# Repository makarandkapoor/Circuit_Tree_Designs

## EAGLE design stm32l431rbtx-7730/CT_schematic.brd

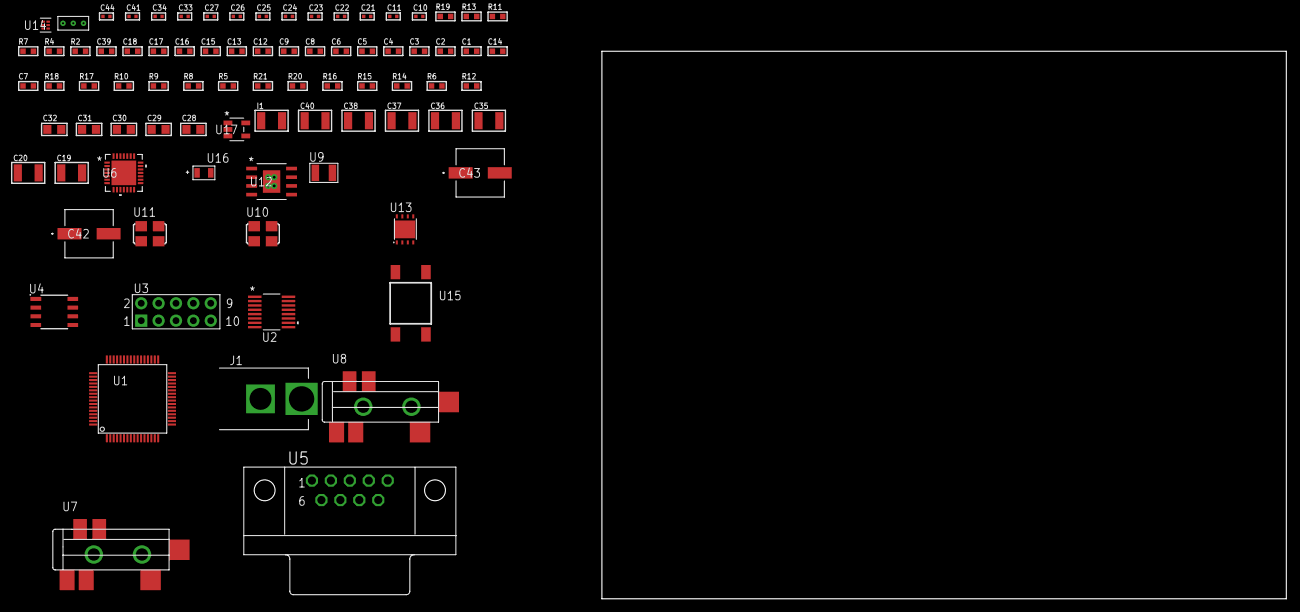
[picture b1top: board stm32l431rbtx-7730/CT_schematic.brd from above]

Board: 2 copper layers, 100.0 x 80.0 mm, 83 parts (0 on the bottom side), 45 nets, no tracks yet.

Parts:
C1, C9, C12, C13, C15, C16, C17, C18, C39: 1e-06; C0603
C2, C3, C4, C5, C6: 1e-07; C0603
C7: 4.7e-06; C0603
C8: 1e-08; C0603
C10, C11: 1e-11; C0402
C14: 2.2e-07; C0603
C19, C20: 2.2e-05; C1210
C21, C22: 1e-09; C0402
C23, C24, C25, C26, C27, C41: 1e-07; C0402
C28, C29, C30, C31, C32: 1e-05; C0805
C33, C34, C44: 1e-08; C0402
C35, C36, C37, C38, C40: 1e-05; C1210
C42, C43: 0.0001; EXV-9H
I1: 1e-05; L1210
J1: PJ-037B; PJ-037B_PACKAGE
R2: 1000.0; R0603
R4: 4700.0; R0603
R5, R17, R18: 10000.0; R0603
R6, R14, R16: 100000.0; R0603
R7: 120.0; R0603
R8, R9, R10: 47000.0; R0603
R11: 680.0; R0603
R12: 4031.5447154472; R0603
R13: 2200.0; R0603
R15: 300000.0; R0603
R19: 9100.0; R0603
R20: 680000.0; R0603
R21: 120000.0; R0603
U1: STM32L431RBT6; LQFP64
U2: LTC2804CGN-1#PBF; SSOP-16
U3: HTSS-105-01-G-D
U4: MCP2562-E/SN; SOIC-8
U5: 182-009-113R531; 182-009-MALE
U6: WM8731CLSEFL; QFN-28
U7, U8: SJ-43515TS-SMT-TR
U9: ABS07-32.768KHZ-7-T
U10: ASFL1-12.288MHZ-EC-T; ASFL1
U11: ASFL1-25MHZ-NCS; ASFL1
U12: MIC5234YME; SOIC-8_EP
U13: LP2951ACSDX/NOPB; WSON-8
U14: TPS3895ADRYR; SON-6
U15: 4-1437565-2; SW_4-1437565-2
U16: Q65110A2395; LGM67K-G1J2-24-Z
U17: nc7sz125m5x; NC7SZ125M5X
U18: Dummy; DUMMY_PACKAGE_176

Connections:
CLK_CRYSTAL_U1_3: C10.1, U1.3, U9.1
CLK_CRYSTAL_U1_4: C11.1, U1.4, U9.2
CLK_U1_5: U1.5, U11.3
CLK_U6_1: U6.1, U10.3
GND: C1.2, C2.2, C3.2, C4.2, C5.2, C6.2, C7.2, C8.2, C9.2, C10.2, C11.2, C12.2, C13.2, C15.2, C16.2, C17.2, C18.2, C22.2, C23.2, C24.2, C25.2, C26.2, C27.2, C28.2, C29.2, C30.2, C31.2, C32.2, C33.2, C34.2, C35.2, C36.2, C37.2, C38.2, C39.2, C40.2, C41.2, C42.2, C43.2, C44.2, J1.2, R2.2, R5.2, R8.2, R9.2, R10.2, R13.2, R16.2, R19.2, R21.2, U1.12, U1.18, U1.31, U1.47, U1.63, U2.8, U3.9, U4.2, U4.8, U5.5, U6.4, U6.15, U6.19, U6.25, U6.26, U6.29, U7.1, U8.1, U10.2, U11.2, U12.7, U12.EPAD, U13.3, U13.4, U13.PAD, U14.2, U16.C, U17.1, U17.3, U18.1
NET_U1_7: R4.1, U1.7, U17.4
NET_U1_60: R5.1, U1.60
NET_U1_62: U15.3, U15.4
NET_U2_6: C12.1, U2.6
NET_U2_7: C14.1, I1.2, U2.7
NET_U2_9: C13.1, U2.9
NET_U2_10: C14.2, U2.10
NET_U2_11: R6.1, U2.11
NET_U3_3: U2.1, U3.3
NET_U3_4: U2.2, U3.4
NET_U3_5: U2.3, U3.5
NET_U3_6: U2.4, U3.6
NET_U4_6: R7.2, U4.6
NET_U5_2: R7.2, U4.6, U5.2
NET_U5_3: R7.1, U4.7, U5.3
NET_U6_20: C27.1, C32.1, U6.20
NET_U7_2: C20.1, R9.1, U7.2
NET_U7_5: C19.1, R8.1, U7.5
NET_U8_5: C21.1, C22.1, R10.1, R11.1, U8.5
NET_U12_4: R12.2, R13.1, U12.4
NET_U13_5: R14.1, U13.5
NET_U13_7: R15.2, R16.1, U13.7
NET_U14_1: R18.1, R19.1, U14.1
NET_U14_3: R20.2, R21.1, U14.3
NET_U14_4: R17.1, U14.4, U17.2
NET_U15_1: R2.1, U15.1, U15.2
PROC_ADC1_IN3: U1.10, U18.2
PROC_ADC1_IN10: U1.21, U18.3
PROC_CAN1_RX: U1.44, U4.4
PROC_CAN1_TX: U1.45, U4.1
PROC_LPUART1_CTS: U1.22, U2.13
PROC_LPUART1_RTS: U1.27, U2.15
PROC_LPUART1_RX: U1.8, U2.16
PROC_LPUART1_TX: U1.9, U2.14
PROC_SAI1_FS_A: U1.33, U6.9, U6.11
PROC_SAI1_SCK_A: U1.29, U6.7
PROC_SAI1_SD_A: U1.11, U6.8
VCC_S1_9V5: C35.1, C36.1, C39.1, C42.1, C43.1, J1.1, U12.5, U12.8, U13.8
VCC_TIER1_3V3: C1.1, C2.1, C3.1, C4.1, C5.1, C6.1, C7.1, C8.1, C9.1, C15.1, C16.1, C18.1, C23.1, C24.1, C25.1, C26.1, C28.1, C29.1, C30.1, C31.1, C33.1, C34.1, C37.1, C38.1, C41.1, C44.1, I1.1, R4.2, R6.2, R12.1, R17.2, R18.2, R20.1, U1.1, U1.13, U1.19, U1.32, U1.48, U1.64, U2.5, U2.12, U4.5, U6.3, U6.5, U6.12, U6.18, U10.4, U11.4, U12.1, U14.6, U17.5
VCC_TIER1_5V0: C17.1, C40.1, R14.2, R15.1, U4.3, U13.1

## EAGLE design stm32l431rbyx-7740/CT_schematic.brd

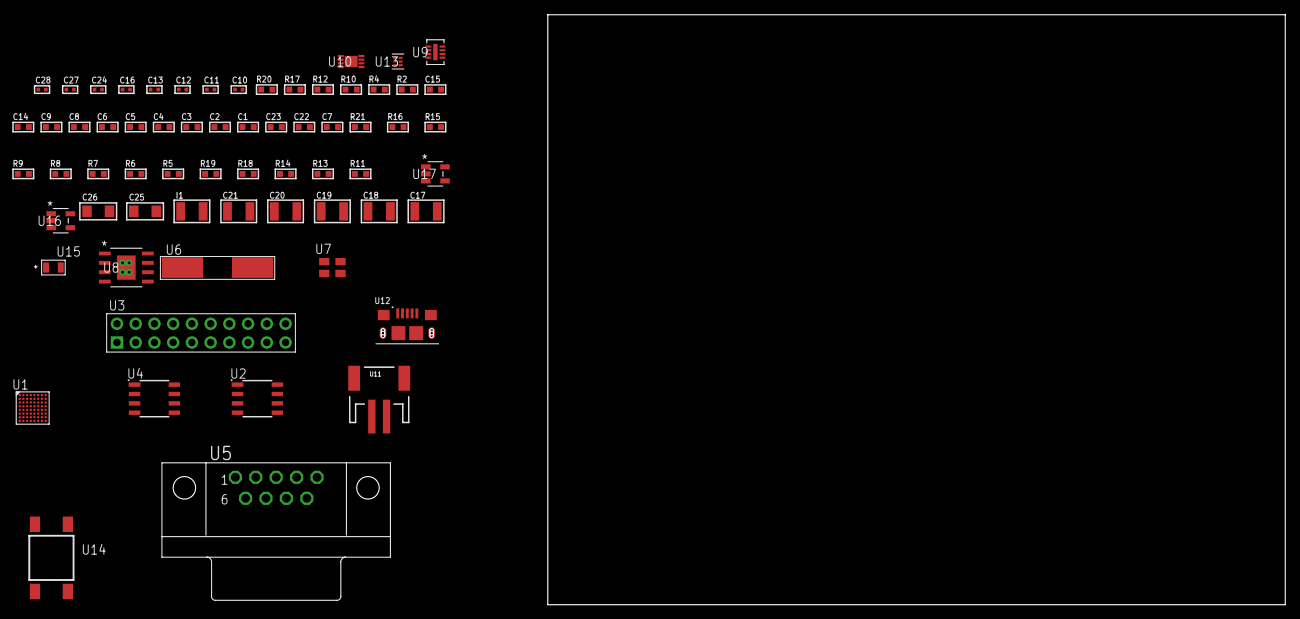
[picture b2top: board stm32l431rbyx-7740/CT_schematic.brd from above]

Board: 2 copper layers, 122.6 x 80.0 mm, 65 parts (0 on the bottom side), 37 nets, no tracks yet.

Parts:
C1, C9, C14, C15: 1e-06; C0603
C2, C3, C4, C5, C6: 1e-07; C0603
C7: 4.7e-06; C0603
C8: 1e-08; C0603
C10, C11: 1e-11; C0402
C12, C16, C27, C28: 1e-08; C0402
C13, C24: 1e-07; C0402
C17, C18, C19, C20, C21: 1e-05; C1210
C22: 2.2e-06; C0603
C23: 2.2e-07; C0603
C25, C26: 1e-05; C1206
I1: 1e-05; L1210
R2: 1000.0; R0603
R4: 4700.0; R0603
R5, R6, R7, R8, R9, R15, R16, R21: 10000.0; R0603
R10: 120.0; R0603
R11: 4031.5447154472; R0603
R12: 2200.0; R0603
R13: 100000.0; R0603
R14: 560000.0; R0603
R17: 9100.0; R0603
R18: 680000.0; R0603
R19: 120000.0; R0603
R20: 2000.0; R0603
U1: STM32L431RBY6; WLCSP64
U2: AT25M01-SSHM-T; SOIC-8
U3: TST-110-05-T-D-RA
U4: MCP2562-E/SN; SOIC-8
U5: 182-009-113R531; 182-009-MALE
U6: ABLS-25.000MHZ-B2F-T
U7: ASEK-32.768KHz-ECST; ASEK
U8: MIC5234YME; SOIC-8_EP
U9: LT3494AEDDB#TRMPBF; DFN-8_DDB
U10: MCP73831T-2ACI/MC; DFN8_2X3MC
U11: S2B-PH-SM4-TB(LF)(SN); JST-2-SMD
U12: 10118193-0001LF; FCI_10118193-0001LF
U13: TPS3895ADRYR; SON-6
U14: 4-1437565-2; SW_4-1437565-2
U15: Q65110A2395; LGM67K-G1J2-24-Z
U16, U17: nc7sz125m5x; NC7SZ125M5X

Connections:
CLK_CRYSTAL_U1_D7: C10.1, U1.D7, U6.1
CLK_CRYSTAL_U1_D8: C11.1, U1.D8, U6.2
CLK_U1_C8: U1.C8, U7.3
GND: C1.2, C2.2, C3.2, C4.2, C5.2, C6.2, C7.2, C8.2, C9.2, C10.2, C11.2, C12.2, C13.2, C14.2, C15.2, C16.2, C17.2, C18.2, C19.2, C20.2, C21.2, C22.2, C23.2, C24.2, C25.2, C26.2, C27.2, C28.2, R2.2, R5.2, R12.2, R17.2, R19.2, R20.2, U1.A7, U1.B1, U1.F8, U1.H2, U1.H8, U2.4, U3.4, U3.6, U3.8, U3.10, U3.12, U3.14, U3.16, U3.18, U3.20, U4.2, U4.8, U5.5, U7.2, U8.7, U8.EPAD, U9.2, U9.9, U10.6, U10.9, U11.2, U12.5, U12.6, U12.7, U12.8, U12.9, U13.2, U15.C, U16.2, U16.3, U17.1, U17.3
INPUT_USBPOWER_5V: C25.1, R21.2, U10.1, U10.2, U12.1
NET_U1_C5: R5.1, U1.C5
NET_U1_D6: R4.1, U1.D6, U17.4
NET_U1_H6: U14.3, U14.4
NET_U2_3: R6.1, U2.3
NET_U2_7: R8.1, U2.7
NET_U4_6: R10.2, U4.6
NET_U5_2: R10.2, U4.6, U5.2
NET_U5_3: R10.1, U4.7, U5.3
NET_U8_4: R11.2, R12.1, U8.4
NET_U9_1: I1.1, U9.1
NET_U9_5: R13.1, U9.5
NET_U9_6: R14.1, U9.6
NET_U9_8: C23.1, U9.8
NET_U10_5: R21.1, U10.5
NET_U10_8: R20.1, U10.8
NET_U13_1: R16.1, R17.1, U13.1
NET_U13_3: R18.2, R19.1, U13.3
NET_U13_4: R15.1, U13.4, U16.4, U17.2
NET_U14_1: R2.1, U14.1, U14.2
PROC_CAN1_RX: U1.C6, U4.4
PROC_CAN1_TX: U1.B6, U4.1
PROC_SPI1_MISO: U1.B4, U2.2
PROC_SPI1_MOSI: U1.C1, U2.5
PROC_SPI1_NSS: R7.1, U1.A2, U2.1
PROC_SPI1_SCK: U1.F5, U2.6
PROC_SYS_JTCK_SWCLK: U1.B2, U3.9
PROC_SYS_JTDO_SWO: U1.A5, U3.13
PROC_SYS_JTMS_SWDIO: U1.C2, U3.7
RST_OUT_U3_SRESET_B: R9.1, U3.15, U16.1
VCC_S1_3V7: C17.1, C18.1, C21.1, C26.1, I1.2, R13.2, U8.5, U8.8, U9.3, U9.4, U10.3, U10.4, U11.1
VCC_TIER1_3V3: C1.1, C2.1, C3.1, C4.1, C5.1, C6.1, C7.1, C8.1, C9.1, C12.1, C13.1, C15.1, C16.1, C19.1, C20.1, C24.1, C27.1, C28.1, R4.2, R6.2, R7.2, R8.2, R9.2, R11.1, R15.2, R16.2, R18.1, U1.A1, U1.A8, U1.B7, U1.G8, U1.H1, U1.H7, U2.8, U3.1, U4.5, U7.4, U8.1, U13.6, U16.5, U17.5
VCC_TIER1_5V0: C14.1, C22.1, R14.2, U4.3, U9.7

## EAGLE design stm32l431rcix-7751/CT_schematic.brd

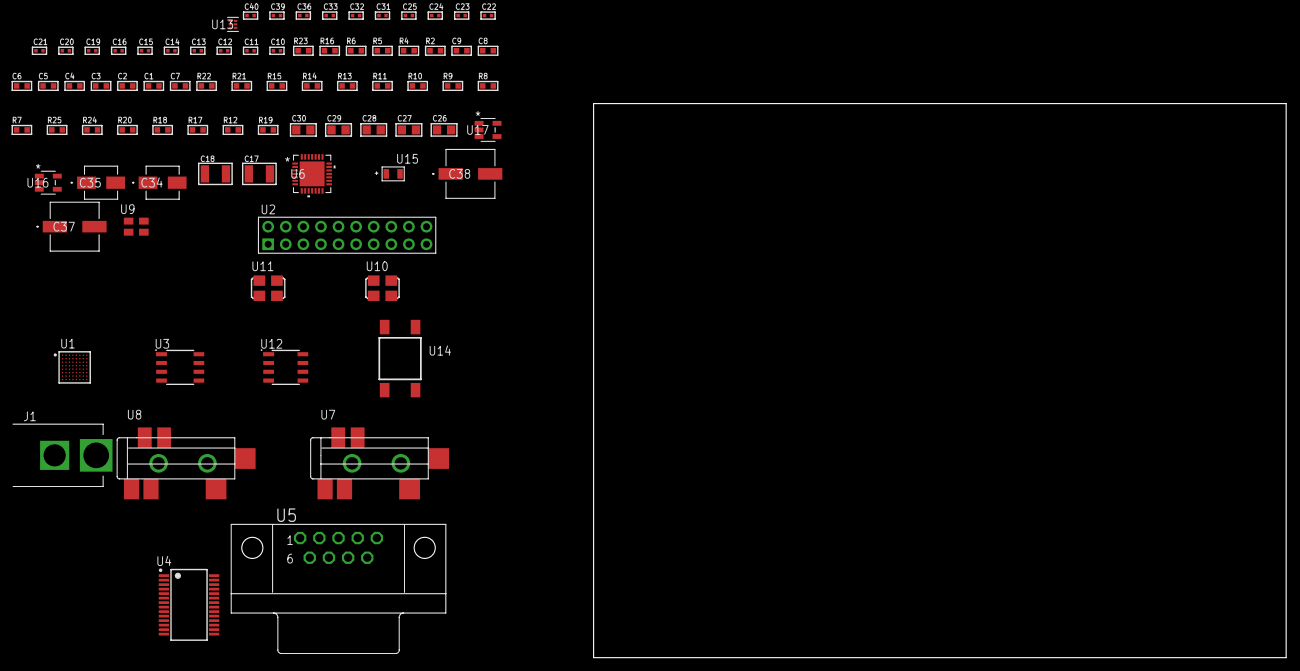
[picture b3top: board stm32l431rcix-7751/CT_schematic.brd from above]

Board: 2 copper layers, 100.0 x 80.0 mm, 81 parts (0 on the bottom side), 43 nets, no tracks yet.

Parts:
C1, C9: 1e-06; C0603
C2, C3, C4, C5, C6: 1e-07; C0603
C7: 4.7e-06; C0603
C8: 1e-08; C0603
C10, C12, C13, C14, C15, C16, C21, C22, C23, C24, C25, C36: 1e-07; C0402
C11, C31, C32, C33, C39, C40: 1e-08; C0402
C17, C18: 2.2e-05; C1210
C19, C20: 1e-09; C0402
C26, C27, C28, C29, C30: 1e-05; C0805
C34: 1e-06; EXV-9B
C35: 2.2e-06; EXV-9B
C37, C38: 0.0001; EXV-9H
J1: PJ-037B; PJ-037B_PACKAGE
R2: 1000.0; R0603
R4: 4700.0; R0603
R5, R6: 2200.0; R0603
R7, R8, R9, R10, R11, R21, R22: 10000.0; R0603
R12, R17, R18, R20: 100000.0; R0603
R13, R14, R15: 47000.0; R0603
R16: 680.0; R0603
R19: 164658.62; R0603
R23: 9100.0; R0603
R24: 680000.0; R0603
R25: 120000.0; R0603
U1: STM32L431RCI6; UFBGA64
U2: TST-110-05-T-D-RA
U3: 24AA1025T-I/SN; SOIC-8
U4: ST3241EBPR; SSOP-28
U5: 182-009-113R531; 182-009-MALE
U6: WM8731CLSEFL; QFN-28
U7, U8: SJ-43515TS-SMT-TR
U9: ASEK-32.768KHz-ECST; ASEK
U10: ASFL1-12.288MHZ-EC-T; ASFL1
U11: ASFL1-25MHZ-NCS; ASFL1
U12: LP2954AIMX/NOPB; LP2954
U13: TPS3895ADRYR; SON-6
U14: 4-1437565-2; SW_4-1437565-2
U15: Q65110A2395; LGM67K-G1J2-24-Z
U16, U17: nc7sz125m5x; NC7SZ125M5X

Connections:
CLK_U1_A1: U1.A1, U9.3
CLK_U1_C1: U1.C1, U11.3
CLK_U6_1: U6.1, U10.3
GND: C1.2, C2.2, C3.2, C4.2, C5.2, C6.2, C7.2, C8.2, C9.2, C10.2, C11.2, C12.2, C15.2, C16.2, C20.2, C21.2, C22.2, C23.2, C24.2, C25.2, C26.2, C27.2, C28.2, C29.2, C30.2, C31.2, C32.2, C33.2, C34.2, C35.2, C36.2, C37.2, C38.2, C39.2, C40.2, J1.2, R2.2, R7.2, R10.2, R13.2, R14.2, R15.2, R20.2, R23.2, R25.2, U1.C2, U1.D4, U1.D5, U1.D6, U1.F1, U2.4, U2.6, U2.8, U2.10, U2.12, U2.14, U2.16, U2.18, U2.20, U3.4, U3.7, U4.23, U4.25, U5.5, U6.4, U6.15, U6.19, U6.25, U6.26, U6.29, U7.1, U8.1, U9.2, U10.2, U11.2, U12.4, U13.2, U15.C, U16.2, U16.3, U17.1, U17.3
NET_U1_A3: R6.1, U1.A3, U3.5
NET_U1_B3: R5.1, U1.B3, U3.6
NET_U1_B4: R7.1, U1.B4
NET_U1_E1: R4.1, U1.E1, U17.4
NET_U1_H8: U14.3, U14.4
NET_U3_1: R10.1, U3.1
NET_U3_2: R11.1, U3.2
NET_U3_3: R9.1, U3.3
NET_U4_1: C14.1, U4.1
NET_U4_2: C14.2, U4.2
NET_U4_3: C16.1, U4.3
NET_U4_22: R12.1, U4.22
NET_U4_24: C13.2, U4.24
NET_U4_27: C15.1, U4.27
NET_U4_28: C13.1, U4.28
NET_U5_2: U4.4, U5.2
NET_U5_3: U4.9, U5.3
NET_U5_7: U4.5, U5.7
NET_U5_8: U4.10, U5.8
NET_U6_20: C25.1, C30.1, U6.20
NET_U7_2: C18.1, R14.1, U7.2
NET_U7_5: C17.1, R13.1, U7.5
NET_U8_5: C19.1, C20.1, R15.1, R16.1, U8.5
NET_U12_3: R18.1, U12.3
NET_U12_5: R17.1, U12.5
NET_U12_7: R19.2, R20.1, U12.7
NET_U13_1: R22.1, R23.1, U13.1
NET_U13_3: R24.2, R25.1, U13.3
NET_U13_4: R21.1, U13.4, U16.4, U17.2
NET_U14_1: R2.1, U14.1, U14.2
PROC_SAI1_FS_A: U1.C7, U6.9, U6.11
PROC_SAI1_SCK_A: U1.D7, U6.7
PROC_SAI1_SD_A: U1.C6, U6.8
PROC_SYS_JTCK_SWCLK: U1.A7, U2.9
PROC_SYS_JTDO_SWO: U1.A5, U2.13
PROC_SYS_JTMS_SWDIO: U1.A8, U2.7
RST_OUT_U2_SRESET_B: R8.1, U2.15, U16.1
VCC_S1_6V7: C34.1, C37.1, C38.1, J1.1, R18.2, U12.8
VCC_TIER1_3V3: C1.1, C2.1, C3.1, C4.1, C5.1, C6.1, C7.1, C8.1, C9.1, C10.1, C11.1, C12.1, C21.1, C22.1, C23.1, C24.1, C26.1, C27.1, C28.1, C29.1, C31.1, C32.1, C33.1, C35.1, C36.1, C39.1, C40.1, R4.2, R5.2, R6.2, R8.2, R9.2, R11.2, R12.2, R17.2, R19.1, R21.2, R22.2, R24.1, U1.B2, U1.D2, U1.E4, U1.E5, U1.E6, U1.H1, U2.1, U3.8, U4.26, U6.3, U6.5, U6.12, U6.18, U9.4, U10.4, U11.4, U12.1, U13.6, U16.5, U17.5

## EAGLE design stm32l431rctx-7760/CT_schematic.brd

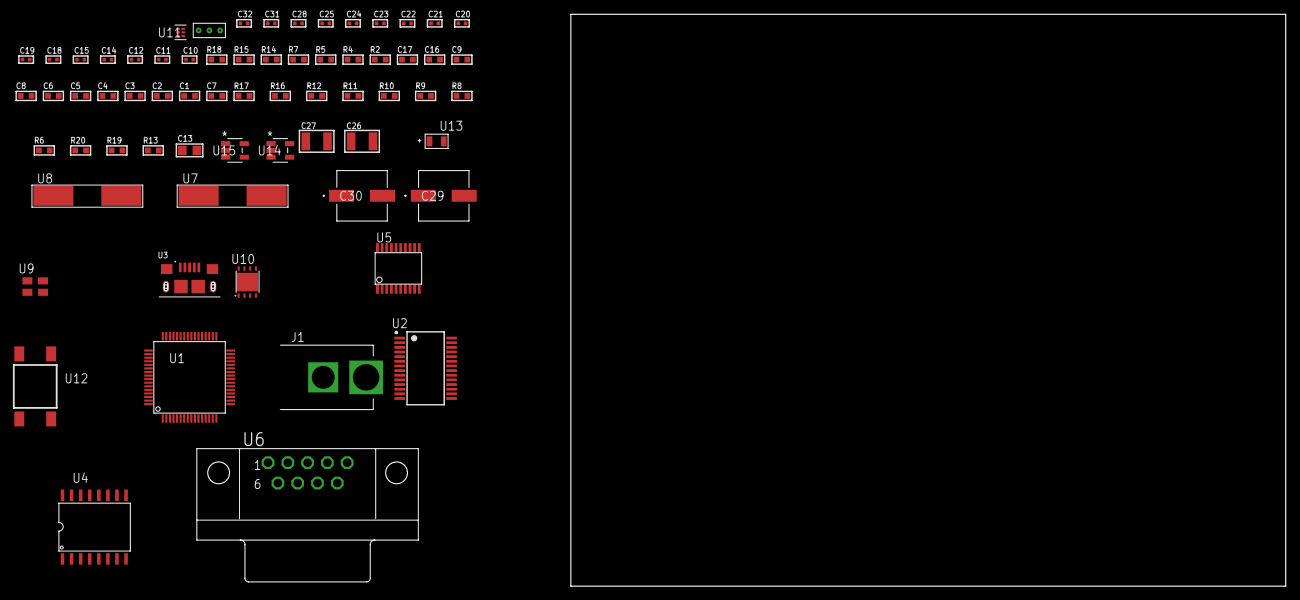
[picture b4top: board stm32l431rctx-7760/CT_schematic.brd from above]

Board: 2 copper layers, 67 parts (0 on the bottom side), 51 nets, no tracks yet.

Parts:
C1, C9, C16, C17: 1e-06; C0603
C2, C3, C4, C5, C6: 1e-07; C0603
C7: 4.7e-06; C0603
C8: 1e-08; C0603
C10, C11: 1e-11; C0402
C12, C14, C15, C18, C19, C20, C21, C22, C23, C28: 1e-07; C0402
C13: 4.7e-06; C0805
C24, C25, C31, C32: 1e-08; C0402
C26, C27: 1e-05; C1210
C29, C30: 0.0001; EXV-9H
J1: PJ-037B; PJ-037B_PACKAGE
R2, R15: 1000.0; R0603
R4, R5, R7: 4700.0; R0603
R6, R8, R9, R10, R11, R12, R16, R17: 10000.0; R0603
R13: 100000.0; R0603
R14: 2231.0; R0603
R18: 9100.0; R0603
R19: 680000.0; R0603
R20: 120000.0; R0603
U1: STM32L431RCT6; LQFP64
U2: FT232RL-REEL; SSOP-28
U3: 10118193-0001LF; FCI_10118193-0001LF
U4: S25FL128SDSMFI000
U5: SP3203ECY-L/TR; TSSOP20-I
U6: 182-009-113R531; 182-009-MALE
U7: ABLS-25.000MHZ-B2F-T
U8: ABLS-12.000MHZ-B4-T
U9: ASEK-32.768KHz-ECST; ASEK
U10: LP3878SDX-ADJ/NOPB; WSON-8
U11: TPS3895ADRYR; SON-6
U12: 4-1437565-2; SW_4-1437565-2
U13: Q65110A2395; LGM67K-G1J2-24-Z
U14, U15: nc7sz125m5x; NC7SZ125M5X
U16: Dummy; DUMMY_PACKAGE_144

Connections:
CLK_CRYSTAL_U1_5: C10.1, U1.5, U7.1
CLK_CRYSTAL_U1_6: C11.1, U1.6, U7.2
CLK_CRYSTAL_U2_27: U2.27, U8.1
CLK_CRYSTAL_U2_28: U2.28, U8.2
CLK_U1_3: U1.3, U9.3
GND: C1.2, C2.2, C3.2, C4.2, C5.2, C6.2, C7.2, C8.2, C9.2, C10.2, C11.2, C12.2, C13.2, C14.2, C15.2, C16.2, C17.2, C18.2, C19.2, C22.2, C23.2, C24.2, C25.2, C26.2, C27.2, C28.2, C29.2, C30.2, C31.2, C32.2, J1.2, R2.2, R6.2, R9.2, R15.2, R18.2, R20.2, U1.12, U1.18, U1.31, U1.47, U1.63, U2.7, U2.18, U2.21, U2.25, U2.26, U3.5, U3.6, U3.7, U3.8, U3.9, U4.10, U5.18, U6.5, U9.2, U10.3, U10.PAD, U11.2, U13.C, U14.1, U14.3, U15.1, U15.3, U16.1
NET_U1_7: R5.1, U1.7, U15.4
NET_U1_60: R6.1, U1.60
NET_U1_62: U12.3, U12.4
NET_U2_14: R8.1, U2.14
NET_U2_17: C14.1, U2.17
NET_U2_19: R9.1, U2.19
NET_U3_1: R7.1, U3.1
NET_U3_2: U2.16, U3.2
NET_U3_3: U2.15, U3.3
NET_U4_3: R4.1, U4.3, U14.4
NET_U5_1: C20.1, U5.1
NET_U5_2: C22.1, U5.2
NET_U5_3: C20.2, U5.3
NET_U5_4: C21.1, U5.4
NET_U5_5: C21.2, U5.5
NET_U5_6: C23.1, U5.6
NET_U6_2: U5.14, U6.2
NET_U6_3: U5.17, U6.3
NET_U6_7: U5.13, U6.7
NET_U6_8: U5.16, U6.8
NET_U10_1: C25.1, U10.1
NET_U10_6: R14.2, R15.1, U10.6
NET_U10_8: R13.1, U10.8
NET_U11_1: R17.1, R18.1, U11.1
NET_U11_3: R19.2, R20.1, U11.3
NET_U11_4: R16.1, U11.4, U14.2, U15.2
NET_U12_1: R2.1, U12.1, U12.2
PROC_LPUART1_CTS: U1.34, U2.3
PROC_LPUART1_RTS: U1.33, U2.11
PROC_LPUART1_RX: U1.8, U2.1
PROC_LPUART1_TX: U1.9, U2.5
PROC_PC13: U1.2, U16.2
PROC_PC15_OSC32_OUT_PC15: U1.4, U16.3
PROC_QUADSPI_BK1_IO0: U1.27, U4.15
PROC_QUADSPI_BK1_IO1: U1.26, U4.8
PROC_QUADSPI_BK1_IO2: R11.1, U1.23, U4.9
PROC_QUADSPI_BK1_IO3: R12.1, U1.22, U4.1
PROC_QUADSPI_BK1_NCS: R10.1, U1.16, U4.7
PROC_QUADSPI_CLK: U1.17, U4.16
PROC_USART1_CTS: U1.44, U5.8
PROC_USART1_RTS: U1.45, U5.10
PROC_USART1_RX: U1.43, U5.11
PROC_USART1_TX: U1.42, U5.7
VCC_S1_13V3: C26.1, C29.1, C30.1, J1.1, R13.2, U10.4
VCC_TIER1_3V3: C1.1, C2.1, C3.1, C4.1, C5.1, C6.1, C7.1, C8.1, C9.1, C12.1, C13.1, C15.1, C16.1, C17.1, C18.1, C19.1, C24.1, C27.1, C28.1, C31.1, C32.1, R4.2, R5.2, R8.2, R10.2, R11.2, R12.2, R14.1, R16.2, R17.2, R19.1, U1.1, U1.13, U1.19, U1.32, U1.48, U1.64, U2.4, U2.20, U4.2, U4.14, U5.12, U5.19, U9.4, U10.5, U11.6, U14.5, U15.5

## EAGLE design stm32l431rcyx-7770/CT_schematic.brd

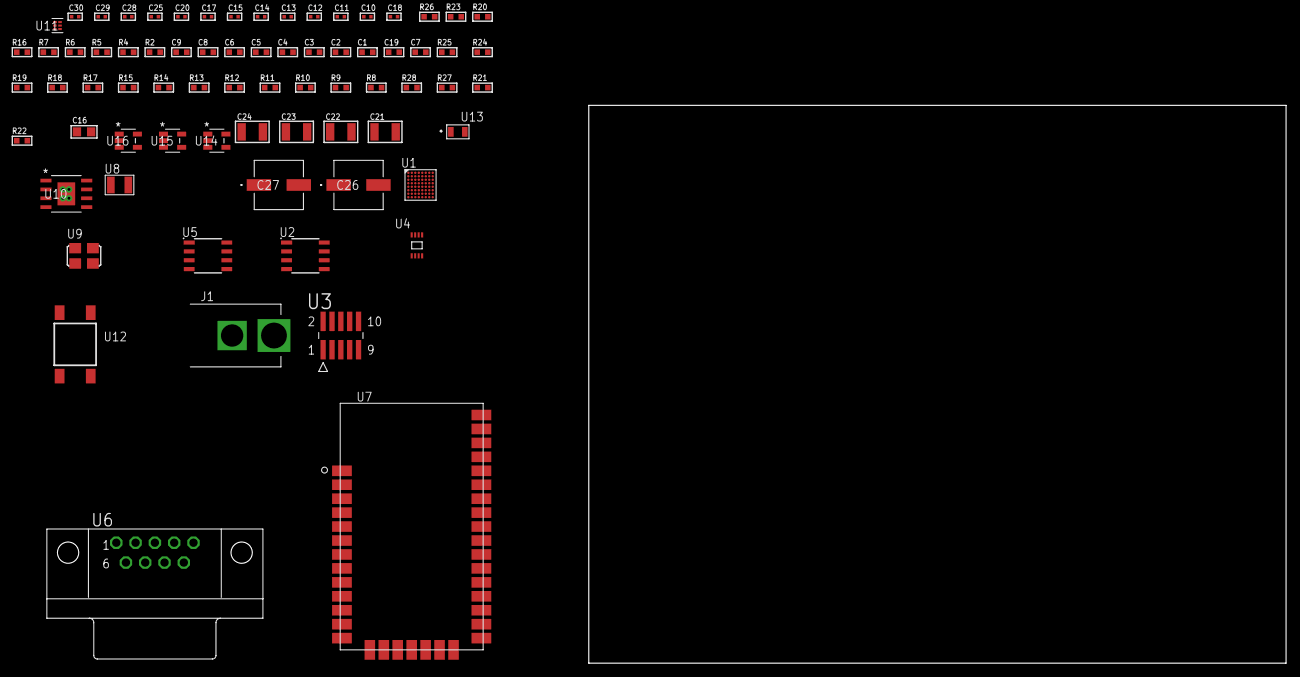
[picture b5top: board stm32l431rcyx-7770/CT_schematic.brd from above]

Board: 2 copper layers, 100.0 x 80.0 mm, 73 parts (0 on the bottom side), 42 nets, no tracks yet.

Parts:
C1, C9: 1e-06; C0603
C2, C3, C4, C5, C6: 1e-07; C0603
C7: 4.7e-06; C0603
C8: 1e-08; C0603
C10, C11: 1e-11; C0402
C12, C14, C20, C28, C29, C30: 1e-08; C0402
C13, C15, C17, C25: 1e-07; C0402
C16: 1e-05; C0805
C18: 4.7e-11; C0402
C19: 8.2e-12; C0603
C21, C22, C23, C24: 1e-05; C1210
C26, C27: 0.0001; EXV-9H
J1: PJ-037B; PJ-037B_PACKAGE
R2: 1000.0; R0603
R4, R5: 4700.0; R0603
R6, R7, R23: 2200.0; R0603
R8, R9, R10, R11, R12, R13, R14, R15, R17, R18, R19, R24, R25: 10000.0; R0603
R16: 5.0; R0603
R20: 120.0; R0603
R21: 470000.0; R0603
R22: 4031.5447154472; R0603
R26: 9100.0; R0603
R27: 680000.0; R0603
R28: 120000.0; R0603
U1: STM32L431RCY6; WLCSP64
U2: AT25020B-SSHL-T; SOIC-8
U3: FTSH-105-01-L-DV-K; SAMTEC_FTSH-105-01-L-DV-K
U4: 24AA32AT-I/MNY; TDFN-8/6MM
U5: SN65HVD230D; SOIC-8
U6: 182-009-113R531; 182-009-MALE
U7: XB24CZ7UIS-004
U8: ABS07-32.768KHZ-7-T
U9: ASFL1-25MHZ-NCS; ASFL1
U10: MIC5234YME; SOIC-8_EP
U11: TPS3895ADRYR; SON-6
U12: 4-1437565-2; SW_4-1437565-2
U13: Q65110A2395; LGM67K-G1J2-24-Z
U14, U15, U16: nc7sz125m5x; NC7SZ125M5X

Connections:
CLK_CRYSTAL_U1_C7: C10.1, U1.C7, U8.1
CLK_CRYSTAL_U1_C8: C11.1, U1.C8, U8.2
CLK_U1_D8: U1.D8, U9.3
GND: C1.2, C2.2, C3.2, C4.2, C5.2, C6.2, C7.2, C8.2, C9.2, C10.2, C11.2, C12.2, C13.2, C14.2, C15.2, C16.2, C17.2, C18.2, C19.2, C20.2, C21.2, C22.2, C23.2, C24.2, C25.2, C26.2, C27.2, C28.2, C29.2, C30.2, J1.2, R2.2, R8.2, R15.2, R16.2, R17.2, R19.2, R21.2, R23.2, R26.2, R28.2, U1.A7, U1.B1, U1.F8, U1.H2, U1.H8, U2.4, U3.3, U3.5, U4.4, U5.2, U6.5, U7.1, U7.11, U7.13, U7.22, U7.35, U9.2, U10.7, U10.EPAD, U11.2, U13.C, U14.2, U14.3, U15.1, U15.3, U16.1, U16.3
NET_U1_A6: R7.1, U1.A6, U4.5
NET_U1_B5: R6.1, U1.B5, U4.6
NET_U1_C5: R8.1, U1.C5
NET_U1_D6: R5.1, U1.D6, U16.4
NET_U1_H6: U12.3, U12.4
NET_U2_3: R9.1, U2.3
NET_U2_7: R11.1, U2.7
NET_U3_9: R16.1, U3.9
NET_U4_1: R17.1, U4.1
NET_U4_2: R18.1, U4.2
NET_U4_3: R19.1, U4.3
NET_U5_6: R20.2, U5.6
NET_U5_8: R21.1, U5.8
NET_U6_2: R20.2, U5.6, U6.2
NET_U6_3: R20.1, U5.7, U6.3
NET_U7_6: R4.1, U7.6, U15.4
NET_U10_4: R22.2, R23.1, U10.4
NET_U11_1: R25.1, R26.1, U11.1
NET_U11_3: R27.2, R28.1, U11.3
NET_U11_4: R24.1, U11.4, U14.4, U15.2, U16.2
NET_U12_1: R2.1, U12.1, U12.2
PROC_CAN1_RX: U1.C6, U5.4
PROC_CAN1_TX: U1.B6, U5.1
PROC_SPI1_MISO: U1.B4, U7.17
PROC_SPI1_MOSI: U1.C1, U7.16
PROC_SPI1_NSS: U1.E5, U7.15
PROC_SPI1_SCK: U1.F5, U7.14
PROC_SPI2_MISO: U1.E7, U2.2
PROC_SPI2_MOSI: U1.E6, U2.5
PROC_SPI2_NSS: R10.1, U1.G3, U2.1
PROC_SPI2_SCK: U1.G2, U2.6
PROC_SYS_JTCK_SWCLK: R15.1, U1.B2, U3.4
PROC_SYS_JTDI: R13.1, U1.A2, U3.8
PROC_SYS_JTDO_SWO: U1.A5, U3.6
PROC_SYS_JTMS_SWDIO: R14.1, U1.C2, U3.2
RST_OUT_U3_JTAG_RST_B: R12.1, U3.10, U14.1
VCC_S1_13V2: C21.1, C22.1, C26.1, C27.1, J1.1, U10.5, U10.8
VCC_TIER1_3V3: C1.1, C2.1, C3.1, C4.1, C5.1, C6.1, C7.1, C8.1, C9.1, C12.1, C13.1, C14.1, C15.1, C16.1, C17.1, C18.1, C19.1, C20.1, C23.1, C24.1, C25.1, C28.1, C29.1, C30.1, R4.2, R5.2, R6.2, R7.2, R9.2, R10.2, R11.2, R12.2, R13.2, R14.2, R18.2, R22.1, R24.2, R25.2, R27.1, U1.A1, U1.A8, U1.B7, U1.G8, U1.H1, U1.H7, U2.8, U3.1, U4.7, U4.8, U5.3, U7.2, U7.27, U9.4, U10.1, U11.6, U14.5, U15.5, U16.5

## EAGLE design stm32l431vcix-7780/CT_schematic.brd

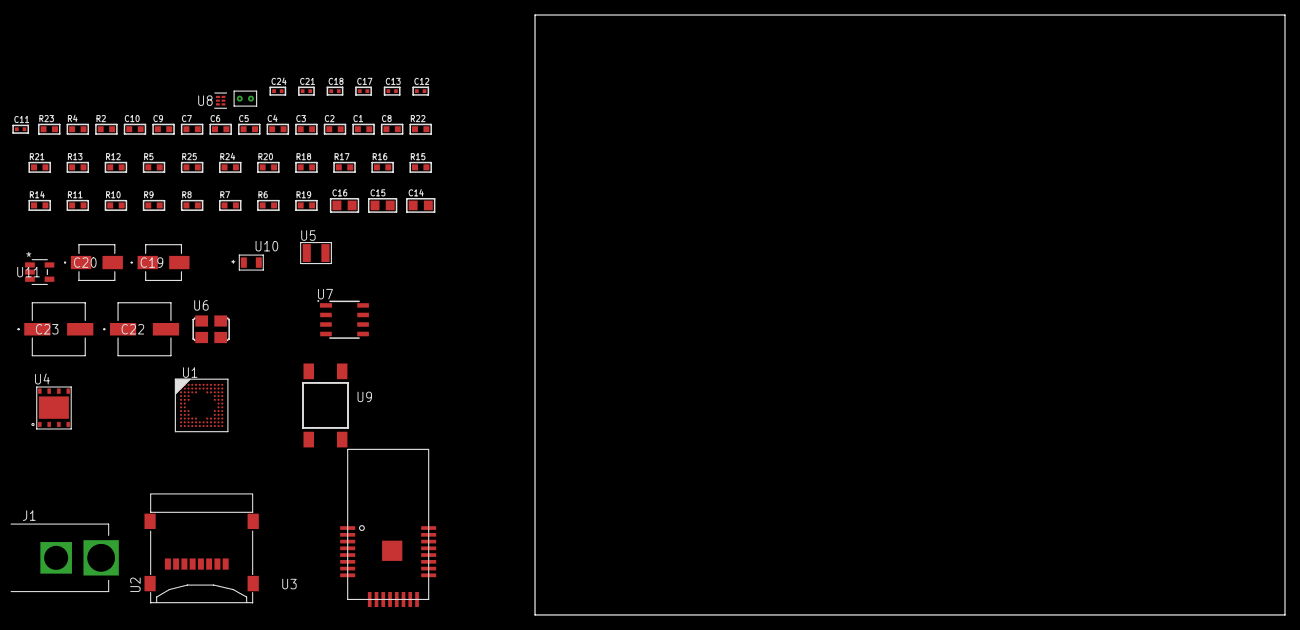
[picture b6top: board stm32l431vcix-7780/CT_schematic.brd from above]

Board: 2 copper layers, 100.0 x 80.0 mm, 60 parts (0 on the bottom side), 36 nets, no tracks yet.

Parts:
C1, C10: 1e-06; C0603
C2, C3, C4, C5, C6, C7: 1e-07; C0603
C8: 4.7e-06; C0603
C9: 1e-08; C0603
C11, C12: 1e-11; C0402
C13, C17, C21: 1e-07; C0402
C14, C15, C16: 1e-05; C0805
C18, C24: 1e-08; C0402
C19: 1e-06; EXV-9B
C20: 2.2e-06; EXV-9B
C22, C23: 0.0001; EXV-9H
J1: PJ-037B; PJ-037B_PACKAGE
R2: 1000.0; R0603
R4: 4700.0; R0603
R5, R12, R13, R21, R22: 10000.0; R0603
R6, R7, R8, R9, R10, R11, R14, R15, R16, R17, R18, R20: 100000.0; R0603
R19: 164658.62; R0603
R23: 9100.0; R0603
R24: 680000.0; R0603
R25: 120000.0; R0603
U1: STM32L431VCI6; UFBGA100
U2: 0472192001; MOLEX_47219-2001
U3: ATBTLC1000-MR110CA
U4: SST26VF032B-104I/MF; WFDN-8
U5: ABS07-32.768KHZ-7-T
U6: ASFL1-25MHZ-NCS; ASFL1
U7: LP2954AIMX/NOPB; LP2954
U8: TPS3895ADRYR; SON-6
U9: 4-1437565-2; SW_4-1437565-2
U10: Q65110A2395; LGM67K-G1J2-24-Z
U11: nc7sz125m5x; NC7SZ125M5X
U12: Dummy; DUMMY_PACKAGE_132

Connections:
CLK_CRYSTAL_U1_D1: C11.1, U1.D1, U5.1
CLK_CRYSTAL_U1_E1: C12.1, U1.E1, U5.2
CLK_U1_F1: U1.F1, U6.3
GND: C1.2, C2.2, C3.2, C4.2, C5.2, C6.2, C7.2, C8.2, C9.2, C10.2, C11.2, C12.2, C13.2, C14.2, C15.2, C16.2, C17.2, C18.2, C19.2, C20.2, C21.2, C22.2, C23.2, C24.2, J1.2, R2.2, R5.2, R20.2, R23.2, R25.2, U1.D3, U1.E3, U1.F2, U1.F11, U1.F12, U1.J1, U1.K1, U2.6, U2.G1, U2.G2, U2.G3, U2.G4, U3.1, U3.9, U3.13, U3.24, U3.25, U4.4, U4.9, U6.2, U7.4, U8.2, U10.C, U11.1, U11.3, U12.1
NET_U1_A4: R5.1, U1.A4
NET_U1_H2: R4.1, U1.H2, U11.4
NET_U1_M1: U1.L1, U1.M1
NET_U1_M12: U9.3, U9.4
NET_U3_17: R12.1, U3.17
NET_U3_20: R13.1, U3.20
NET_U7_3: R18.1, U7.3
NET_U7_5: R17.1, U7.5
NET_U7_7: R19.2, R20.1, U7.7
NET_U8_1: R22.1, R23.1, U8.1
NET_U8_3: R24.2, R25.1, U8.3
NET_U8_4: R21.1, U8.4, U11.2
NET_U9_1: R2.1, U9.1, U9.2
PROC_DAC1_OUT2: U1.K4, U12.2
PROC_QUADSPI_BK1_IO0: U1.L9, U4.5
PROC_QUADSPI_BK1_IO1: U1.M5, U4.2
PROC_QUADSPI_BK1_IO2: R15.1, U1.M4, U4.3
PROC_QUADSPI_BK1_NCS: R14.1, U1.K3, U4.1
PROC_QUADSPI_BK2_IO3: R16.1, U1.A5, U4.7
PROC_QUADSPI_CLK: U1.L3, U4.6
PROC_SDMMC1_CK: R7.1, U1.B10, U2.5
PROC_SDMMC1_CMD: R6.1, U1.C8, U2.3
PROC_SDMMC1_D0: R8.1, U1.E10, U2.7
PROC_SDMMC1_D1: R9.1, U1.D12, U2.8
PROC_SDMMC1_D2: R10.1, U1.B11, U2.1
PROC_SDMMC1_D3: R11.1, U1.C10, U2.2
PROC_SPI1_MISO: U1.A7, U3.14
PROC_SPI1_MOSI: U1.A12, U3.11
PROC_SPI1_NSS: U1.A9, U3.12
PROC_SPI1_SCK: U1.A8, U3.10
VCC_S1_14V1: C19.1, C22.1, C23.1, J1.1, R18.2, U7.8
VCC_TIER1_3V3: C1.1, C2.1, C3.1, C4.1, C5.1, C6.1, C7.1, C8.1, C9.1, C10.1, C13.1, C14.1, C15.1, C16.1, C17.1, C18.1, C20.1, C21.1, C24.1, R4.2, R6.2, R7.2, R8.2, R9.2, R10.2, R11.2, R12.2, R13.2, R14.2, R15.2, R16.2, R17.2, R19.1, R21.2, R22.2, R24.1, U1.C4, U1.C11, U1.E2, U1.G2, U1.G11, U1.G12, U1.H3, U1.M1, U2.4, U3.6, U3.22, U4.8, U6.4, U7.1, U8.6, U11.5

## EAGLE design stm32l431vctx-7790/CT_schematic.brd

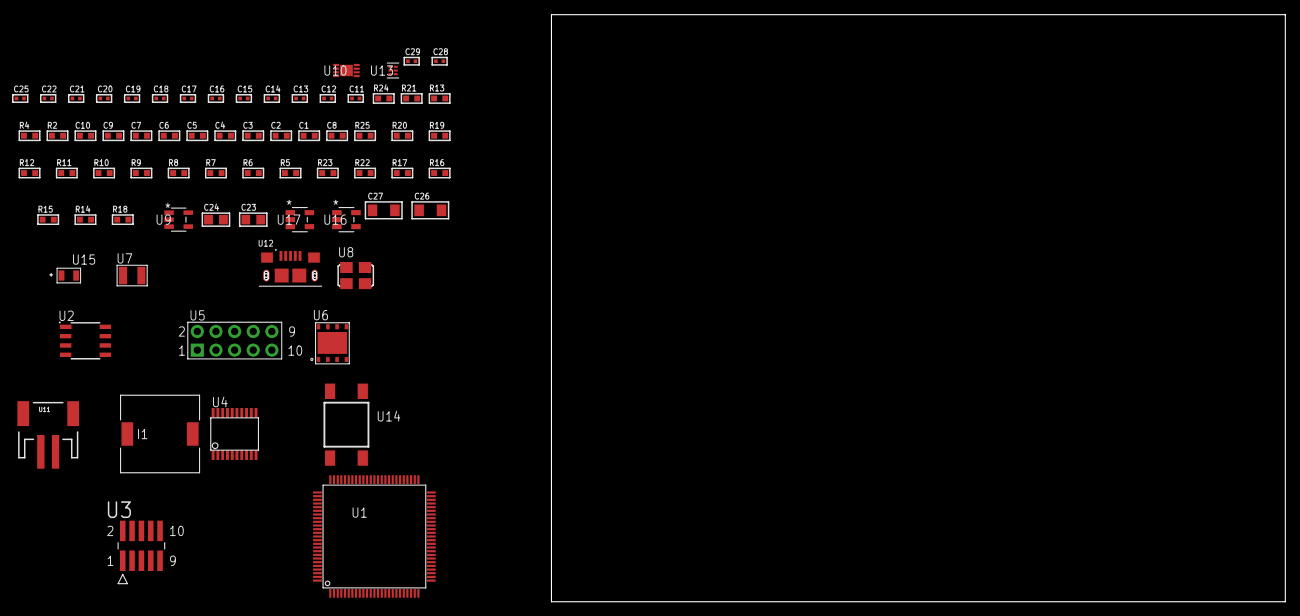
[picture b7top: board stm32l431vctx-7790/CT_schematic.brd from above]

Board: 2 copper layers, 70 parts (0 on the bottom side), 47 nets, no tracks yet.

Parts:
C1, C10: 1e-06; C0603
C2, C3, C4, C5, C6, C7: 1e-07; C0603
C8: 4.7e-06; C0603
C9: 1e-08; C0603
C11, C12: 1e-11; C0402
C13, C22, C28, C29: 1e-08; C0402
C14, C15, C16, C17, C18, C19, C20, C21, C25: 1e-07; C0402
C23, C24: 1e-05; C0805
C26, C27: 1e-05; C1206
I1: 5.2e-06; DR1040
R2: 1000.0; R0603
R4: 4700.0; R0603
R5, R6, R7, R8, R9, R10, R11, R12, R19, R20, R25: 10000.0; R0603
R13: 5.0; R0603
R14, R15, R16: 100000.0; R0603
R17: 220000.0; R0603
R18: 1000000.0; R0603
R21: 9100.0; R0603
R22: 680000.0; R0603
R23: 120000.0; R0603
R24: 2000.0; R0603
U1: STM32L431VCT6; LQFP100
U2: AT25020B-SSHL-T; SOIC-8
U3: FTSH-105-01-L-DV-K; SAMTEC_FTSH-105-01-L-DV-K
U4: SP3203ECY-L/TR; TSSOP20-I
U5: HTSS-105-01-G-D
U6: SST26VF016B-104I/MF; WFDN-8
U7: ABS07-32.768KHZ-7-T
U8: ASFL1-25MHZ-NCS; ASFL1
U9: ltc3406es5; TSOT-23-5
U10: MCP73831T-2ACI/MC; DFN8_2X3MC
U11: S2B-PH-SM4-TB(LF)(SN); JST-2-SMD
U12: 10118193-0001LF; FCI_10118193-0001LF
U13: TPS3895ADRYR; SON-6
U14: 4-1437565-2; SW_4-1437565-2
U15: Q65110A2395; LGM67K-G1J2-24-Z
U16, U17: nc7sz125m5x; NC7SZ125M5X

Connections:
CLK_CRYSTAL_U1_8: C11.1, U1.8, U7.1
CLK_CRYSTAL_U1_9: C12.1, U1.9, U7.2
CLK_U1_12: U1.12, U8.3
GND: C1.2, C2.2, C3.2, C4.2, C5.2, C6.2, C7.2, C8.2, C9.2, C10.2, C11.2, C12.2, C13.2, C14.2, C15.2, C16.2, C19.2, C20.2, C21.2, C22.2, C23.2, C24.1, C24.2, C25.2, C26.2, C27.2, C28.2, C29.2, R2.2, R5.2, R12.2, R13.2, R17.2, R21.2, R23.2, R24.2, U1.10, U1.19, U1.20, U1.27, U1.49, U1.74, U1.99, U2.4, U3.3, U3.5, U4.18, U5.9, U6.4, U6.9, U8.2, U9.2, U10.6, U10.9, U11.2, U12.5, U12.6, U12.7, U12.8, U12.9, U13.2, U15.C, U16.2, U16.3, U17.1, U17.3
INPUT_USBPOWER_5V: C26.1, R25.2, U10.1, U10.2, U12.1
NET_U1_14: R4.1, U1.14, U17.4
NET_U1_94: R5.1, U1.94
NET_U1_98: U14.3, U14.4
NET_U2_3: R6.1, U2.3
NET_U2_7: R8.1, U2.7
NET_U3_9: R13.1, U3.9
NET_U4_1: C17.1, U4.1
NET_U4_2: C19.1, U4.2
NET_U4_3: C17.2, U4.3
NET_U4_4: C18.1, U4.4
NET_U4_5: C18.2, U4.5
NET_U4_6: C20.1, U4.6
NET_U5_3: U4.14, U5.3
NET_U5_4: U4.13, U5.4
NET_U5_5: U4.17, U5.5
NET_U5_6: U4.16, U5.6
NET_U9_3: I1.1, U9.3
NET_U9_5: R17.1, R18.1, U9.5
NET_U9_ATNET_3: I1.2, R18.2
NET_U10_5: R25.1, U10.5
NET_U10_8: R24.1, U10.8
NET_U13_1: R20.1, R21.1, U13.1
NET_U13_3: R22.2, R23.1, U13.3
NET_U13_4: R19.1, U13.4, U16.4, U17.2
NET_U14_1: R2.1, U14.1, U14.2
PROC_QUADSPI_BK1_IO0: U1.36, U6.5
PROC_QUADSPI_BK1_IO1: U1.35, U6.2
PROC_QUADSPI_BK1_IO2: R15.1, U1.32, U6.3
PROC_QUADSPI_BK1_NCS: R14.1, U1.25, U6.1
PROC_QUADSPI_BK2_IO3: R16.1, U1.88, U6.7
PROC_QUADSPI_CLK: U1.26, U6.6
PROC_SPI1_MISO: U1.45, U2.2
PROC_SPI1_MOSI: U1.46, U2.5
PROC_SPI1_NSS: R7.1, U1.29, U2.1
PROC_SPI1_SCK: U1.24, U2.6
PROC_SYS_JTCK_SWCLK: R12.1, U1.76, U3.4
PROC_SYS_JTDI: R10.1, U1.77, U3.8
PROC_SYS_JTDO_SWO: U1.89, U3.6
PROC_SYS_JTMS_SWDIO: R11.1, U1.72, U3.2
RST_OUT_U3_JTAG_RST_B: R9.1, U3.10, U16.1
VCC_S1_3V7: C23.1, C27.1, U9.4, U10.3, U10.4, U11.1
VCC_TIER1_3V3: C1.1, C2.1, C3.1, C4.1, C5.1, C6.1, C7.1, C8.1, C9.1, C10.1, C13.1, C14.1, C15.1, C16.1, C21.1, C22.1, C24.2, C25.1, C28.1, C29.1, I1.2, R4.2, R6.2, R7.2, R8.2, R9.2, R10.2, R11.2, R14.2, R15.2, R16.2, R18.2, R19.2, R20.2, R22.1, U1.6, U1.11, U1.21, U1.22, U1.28, U1.50, U1.73, U1.75, U1.100, U2.8, U3.1, U4.12, U4.19, U6.8, U8.4, U13.6, U16.5, U17.5

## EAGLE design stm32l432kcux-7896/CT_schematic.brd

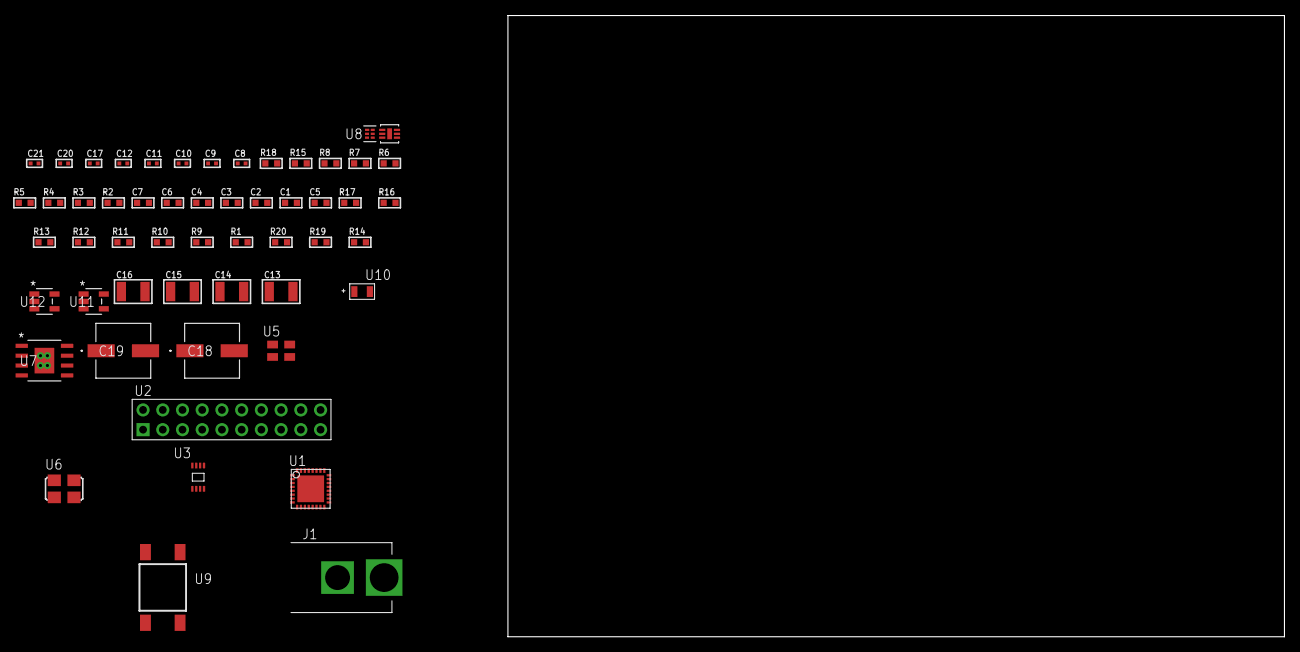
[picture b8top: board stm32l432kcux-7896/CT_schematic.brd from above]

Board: 2 copper layers, 100.0 x 80.0 mm, 54 parts (0 on the bottom side), 24 nets, no tracks yet.

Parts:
C1, C2, C3, C4: 1e-07; C0603
C5: 4.7e-06; C0603
C6: 1e-08; C0603
C7: 1e-06; C0603
C8, C10, C17: 1e-07; C0402
C9, C11, C12, C20, C21: 1e-08; C0402
C13, C14, C15, C16: 1e-05; C1210
C18, C19: 0.0001; EXV-9H
J1: PJ-037B; PJ-037B_PACKAGE
R1, R9, R10, R11, R12, R13, R16, R17: 10000.0; R0603
R2: 1000.0; R0603
R3: 1600.5; R0603
R4: 4700.0; R0603
R5, R6, R7, R8, R15: 2200.0; R0603
R14: 4031.5447154472; R0603
R18: 9100.0; R0603
R19: 680000.0; R0603
R20: 120000.0; R0603
U1: STM32L432KCU6; UFQFPN32
U2: TST-110-05-T-D-RA
U3: 24AA64T-I/MNY; TDFN-8/6MM
U4: SI7006-A20-IM; DFN-6
U5: ASEK-32.768KHz-ECST; ASEK
U6: ASFL1-12MHZ-NCS; ASFL1
U7: MIC5234YME; SOIC-8_EP
U8: TPS3895ADRYR; SON-6
U9: 4-1437565-2; SW_4-1437565-2
U10: Q65110A2395; LGM67K-G1J2-24-Z
U11, U12: nc7sz125m5x; NC7SZ125M5X

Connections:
CLK_U1_2: U1.2, U5.3
CLK_U1_6: U1.6, U6.3
GND: C1.2, C2.2, C3.2, C4.2, C5.2, C6.2, C7.2, C8.2, C9.2, C10.2, C11.2, C12.2, C13.2, C14.2, C15.2, C16.2, C17.2, C18.2, C19.2, C20.2, C21.2, J1.2, R2.2, R9.2, R11.2, R15.2, R18.2, R20.2, U1.16, U1.32, U1.EPAD, U2.4, U2.6, U2.8, U2.10, U2.12, U2.14, U2.16, U2.18, U2.20, U3.4, U3.7, U4.2, U4.7, U5.2, U6.2, U7.7, U7.EPAD, U8.2, U10.C, U11.2, U11.3, U12.1, U12.3
NET_U1_4: R4.1, U1.4, U12.4
NET_U1_13: R7.1, U1.13, U3.6
NET_U1_19: R5.1, U1.19, U4.6
NET_U1_20: R6.1, U1.20, U4.1
NET_U1_27: R8.1, U1.27, U3.5
NET_U1_30: R3.1, U1.30, U10.A
NET_U1_31: R1.1, R9.1, U1.31, U9.3, U9.4
NET_U3_1: R11.1, U3.1
NET_U3_2: R12.1, U3.2
NET_U3_3: R13.1, U3.3
NET_U7_4: R14.2, R15.1, U7.4
NET_U8_1: R17.1, R18.1, U8.1
NET_U8_3: R19.2, R20.1, U8.3
NET_U8_4: R16.1, U8.4, U11.4, U12.2
NET_U9_1: R2.1, U9.1, U9.2
PROC_SYS_JTCK_SWCLK: U1.24, U2.9
PROC_SYS_JTDO_SWO: U1.26, U2.13
PROC_SYS_JTMS_SWDIO: U1.23, U2.7
RST_OUT_U2_SRESET_B: R10.1, U2.15, U11.1
VCC_S1_11V5: C13.1, C14.1, C18.1, C19.1, J1.1, U7.5, U7.8
VCC_TIER1_3V3: C1.1, C2.1, C3.1, C4.1, C5.1, C6.1, C7.1, C8.1, C9.1, C10.1, C11.1, C12.1, C15.1, C16.1, C17.1, C20.1, C21.1, R1.2, R3.2, R4.2, R5.2, R6.2, R7.2, R8.2, R10.2, R12.2, R13.2, R14.1, R16.2, R17.2, R19.1, U1.1, U1.5, U1.17, U2.1, U3.8, U4.5, U5.4, U6.4, U7.1, U8.6, U11.5, U12.5
